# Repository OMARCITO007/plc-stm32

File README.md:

# plc-stm32
PLC básico basado en stm32 como controlador principal, con RS485, WIFI ESP32 y ETHERNET W5500

## Microncontrolador
* ⚛️ STM32F407VGT6.
* 🍏 ESP32-WROOM-32U.

## Voltaje de funcionamiento
* 🔌 24V.
* 🔌 Salida 5V.
## Caracteristicas
* 💙 x2 RS232.
* 💙 x1 RS485.
* 💙 x1 WIFI ESP32.
* 💙 x1 ETHERNET W5500.
* 💙 x1 EEPROM.
* 💙 x1 RTC.
* 💙 x1 USB para actualizar en modo BOOT y datos serial.
* ✔️ x12 entradas.
* ✔️ x16 salidas relé 2A.

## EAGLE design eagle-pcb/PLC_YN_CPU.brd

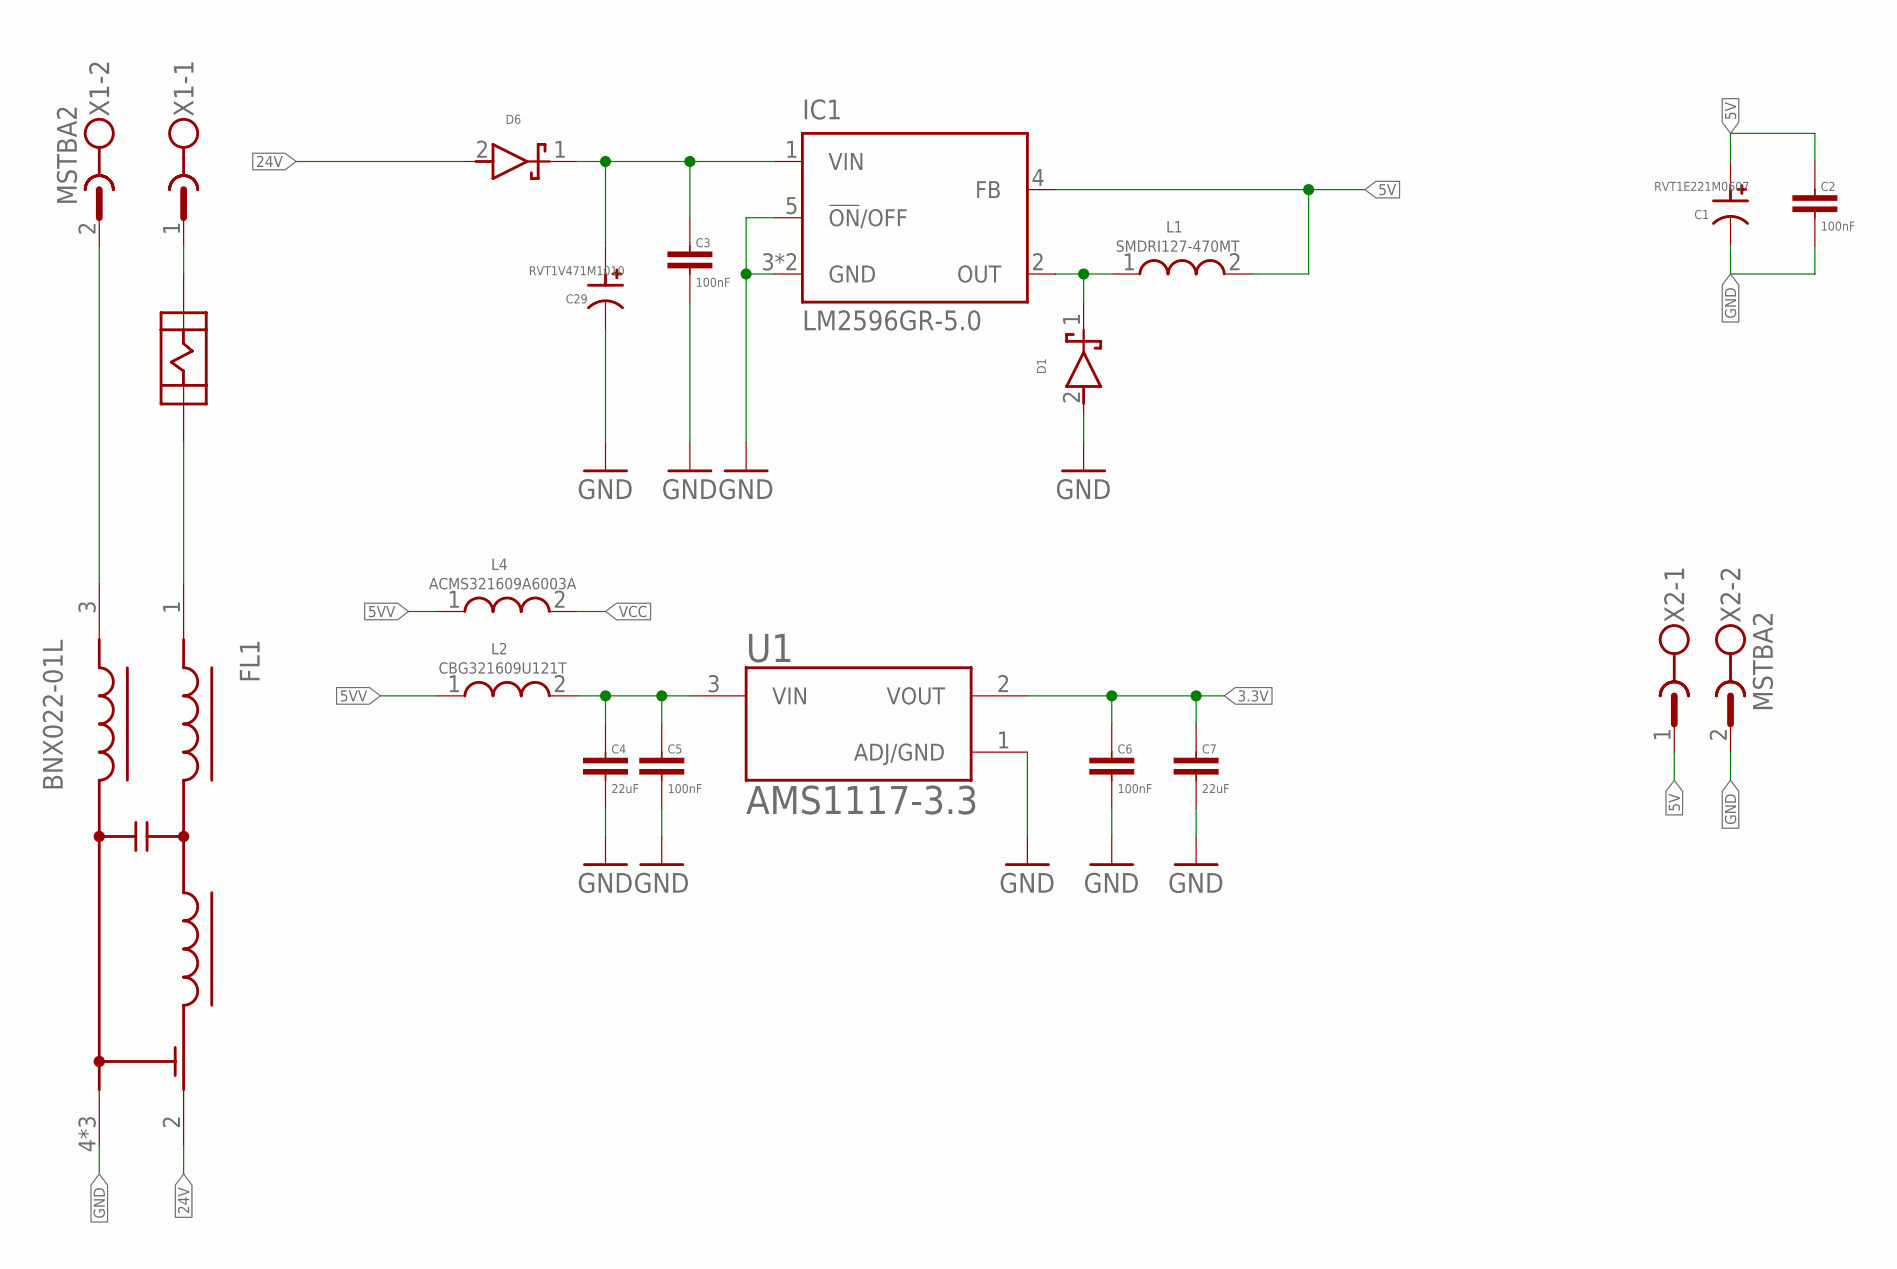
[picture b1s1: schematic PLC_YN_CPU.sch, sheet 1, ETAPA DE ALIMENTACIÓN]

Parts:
C1: RVT1E221M0607; CAP_100UF_6.3X7.7SMD
C2, C3, C5, C6: 100nF; C0603
C4, C7: 22uF; SMD_1206
C29: RVT1V471M1010; CAP_470UF_SMD_10X10.2
D1: SS36F; B360
D6: SS56; B360
F2: 3A; PORTAFUSIBLE
FL1: BNX022-01L; FIL_BNX022-01L
IC1: LM2596GR-5.0; TO263-5
L1: SMDRI127-470MT; IND
L2: CBG321609U121T; SMD_1206
L4: ACMS321609A6003A; SMD_1206
U1: AMS1117-3.3; SOT229P700X180-4N
X1, X2: MSTBA2

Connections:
3.3V: C6.1, C7.1, U1.2 (VOUT); also elsewhere on the board
5V: C1.P (1), C2.1, IC1.4 (FB), L1.2, X2.1; also elsewhere on the board
5VV: L2.1, L4.1; also elsewhere on the board
24V: D6.2, FL1.2 (CB); also elsewhere on the board
GND: C1.N (2), C2.2, C3.2, C4.2, C5.2, C6.2, C7.2, C29.N (2), D1.2, FL1.4 (CG), FL1.5 (CG), FL1.6 (CG), IC1.3 (GND), IC1.5 (!ON!/OFF), IC1.6 (GND), U1.1 (ADJ/GND), X2.2; also elsewhere on the board
unnamed: C4.1, C5.1, L2.2, U1.3 (VIN)
unnamed: C3.1, C29.P (1), D6.1, IC1.1 (VIN)
unnamed: D1.1, IC1.2 (OUT), L1.1
unnamed: F2.P$2, F2.P$4, X1.1
unnamed: FL1.3 (PSG), X1.2
unnamed: F2.P$1, F2.P$3, FL1.1 (B)
VCC: L4.2; also elsewhere on the board

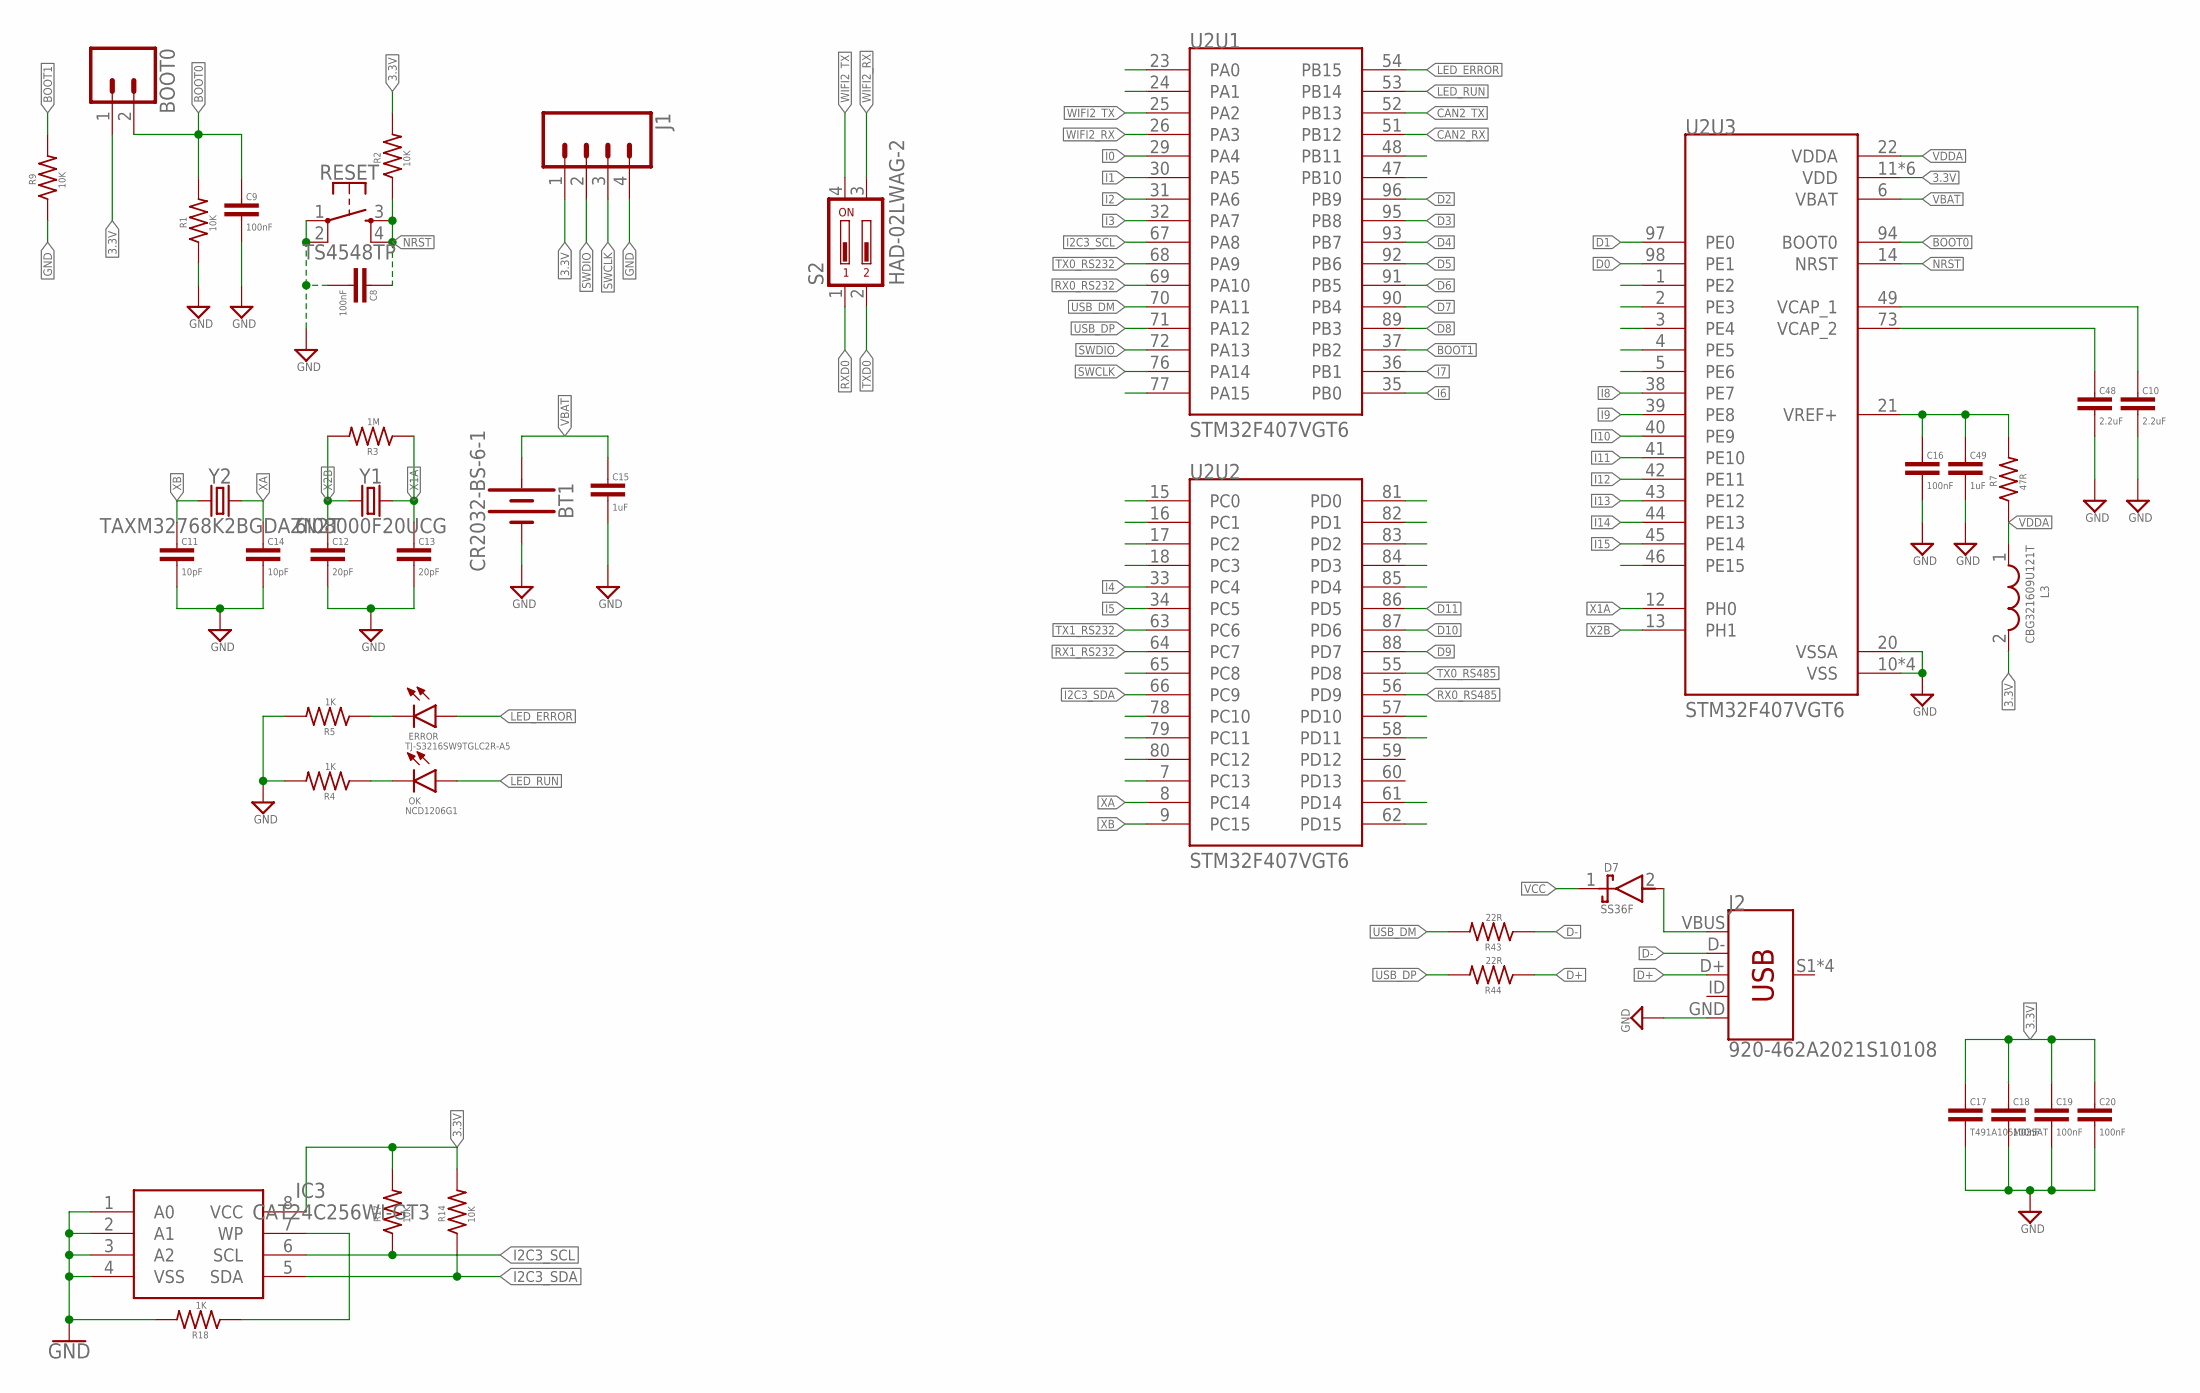
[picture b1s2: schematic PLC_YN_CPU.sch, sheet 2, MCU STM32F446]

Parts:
BOOT0: CONN_02; 1X02
BT1: CR2032-BS-6-1; BAT_CR2032_SMD
C8, C9, C16, C18, C19, C20: 100nF; C0603
C10, C48: 2.2uF; C0603
C11, C14: 10pF; C0603
C12, C13: 20pF; C0603
C15: 1uF; SMD_1206
C17: T491A105M035AT; SMD_1206
C49: 1uF; C0603
D7: SS36F; B360
ERROR: TJ-S3216SW9TGLC2R-A5; L1206
IC3: CAT24C256WI-GT3; SO08
J1: CONN_04; 1X04
J2: 920-462A2021S10108; USB-MINIB
L3: CBG321609U121T; SMD_1206
OK: NCD1206G1; L1206
R1, R2, R9, R14, R17: 10K; R0603
R3: 1M; R0603
R4, R5, R18: 1K; R0603
R7: 47R; R0603
R43, R44: 22R; R0603
RESET: TS4548TP; SWITCH
S2: HAD-02LWAG-2; CTS-219-02
U2: STM32F407VGT6; QFP50P1600X1600X160-100N
Y1: 6I08000F20UCG; CRYSTAL-SMD-5X3.2-2PAD
Y2: TAXM32768K2BGDAZN2T; CRYSTAL-SMD-2X6-CYL

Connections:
3.3V: BOOT0.1, C17.1, C18.1, C19.1, C20.1, IC3.8 (VCC), J1.1, L3.2, R2.2, R14.2, R17.2, U2.11 (VDD), U2.19 (VDD), U2.28 (VDD), U2.50 (VDD), U2.75 (VDD), U2.100 (VDD); also elsewhere on the board
BOOT0: BOOT0.2, C9.1, R1.2, U2.94 (BOOT0)
BOOT1: R9.2, U2.37 (PB2)
CAN2_RX: U2.51 (PB12)
CAN2_TX: U2.52 (PB13)
D0: U2.98 (PE1); also elsewhere on the board
D1: U2.97 (PE0); also elsewhere on the board
D2: U2.96 (PB9); also elsewhere on the board
D3: U2.95 (PB8); also elsewhere on the board
D4: U2.93 (PB7); also elsewhere on the board
D5: U2.92 (PB6); also elsewhere on the board
D6: U2.91 (PB5); also elsewhere on the board
D7: U2.90 (PB4); also elsewhere on the board
D8: U2.89 (PB3); also elsewhere on the board
D9: U2.88 (PD7); also elsewhere on the board
D10: U2.87 (PD6); also elsewhere on the board
D11: U2.86 (PD5); also elsewhere on the board
D+: J2.D+, R44.1
D-: J2.D-, R43.1
GND: BT1.N (-), C8.2, C9.2, C10.2, C11.2, C12.2, C13.2, C14.2, C15.2, C16.2, C17.2, C18.2, C19.2, C20.2, C48.2, C49.2, IC3.1 (A0), IC3.2 (A1), IC3.3 (A2), IC3.4 (VSS), J1.4, J2.GND, R1.1, R4.2, R5.2, R9.1, R18.2, RESET.1, RESET.2, U2.10 (VSS), U2.20 (VSSA), U2.27 (VSS), U2.74 (VSS), U2.99 (VSS); also elsewhere on the board
I0: U2.29 (PA4); also elsewhere on the board
I1: U2.30 (PA5); also elsewhere on the board
I2: U2.31 (PA6); also elsewhere on the board
I2C3_SCL: IC3.6 (SCL), R17.1, U2.67 (PA8)
I2C3_SDA: IC3.5 (SDA), R14.1, U2.66 (PC9)
I3: U2.32 (PA7); also elsewhere on the board
I4: U2.33 (PC4); also elsewhere on the board
I5: U2.34 (PC5); also elsewhere on the board
I6: U2.35 (PB0); also elsewhere on the board
I7: U2.36 (PB1); also elsewhere on the board
I8: U2.38 (PE7); also elsewhere on the board
I9: U2.39 (PE8); also elsewhere on the board
I10: U2.40 (PE9); also elsewhere on the board
I11: U2.41 (PE10); also elsewhere on the board
I12: U2.42 (PE11); also elsewhere on the board
I13: U2.43 (PE12); also elsewhere on the board
I14: U2.44 (PE13); also elsewhere on the board
I15: U2.45 (PE14); also elsewhere on the board
LED_ERROR: ERROR.A, U2.54 (PB15)
LED_RUN: OK.A, U2.53 (PB14)
unnamed: C10.1, U2.49 (VCAP_1)
unnamed: C48.1, U2.73 (VCAP_2)
unnamed: C16.1, C49.1, R7.2, U2.21 (VREF+)
unnamed: D7.2, J2.VBUS
unnamed: IC3.7 (WP), R18.1
unnamed: ERROR.C, R5.1
unnamed: OK.C, R4.1
NRST: C8.1, R2.1, RESET.3, RESET.4, U2.14 (NRST)
RX0_RS232: U2.69 (PA10); also elsewhere on the board
RX0_RS485: U2.56 (PD9); also elsewhere on the board
RX1_RS232: U2.64 (PC7); also elsewhere on the board
RXD0: S2.1; also elsewhere on the board
SWCLK: J1.3, U2.76 (PA14)
SWDIO: J1.2, U2.72 (PA13)
TX0_RS232: U2.68 (PA9); also elsewhere on the board
TX0_RS485: U2.55 (PD8); also elsewhere on the board
TX1_RS232: U2.63 (PC6); also elsewhere on the board
TXD0: S2.2; also elsewhere on the board
USB_DM: R43.2, U2.70 (PA11)
USB_DP: R44.2, U2.71 (PA12)
VBAT: BT1.P (+), C15.1, U2.6 (VBAT)
VCC: D7.1; also elsewhere on the board
VDDA: L3.1, R7.1, U2.22 (VDDA)
WIFI2_RX: S2.3, U2.26 (PA3)
WIFI2_TX: S2.4, U2.25 (PA2)
X1A: C13.1, R3.1, U2.12 (PH0), Y1.P$2 (2)
X2B: C12.1, R3.2, U2.13 (PH1), Y1.P$1 (1)
XA: C14.1, U2.8 (PC14), Y2.X2 (2)
XB: C11.1, U2.9 (PC15), Y2.X1 (1)

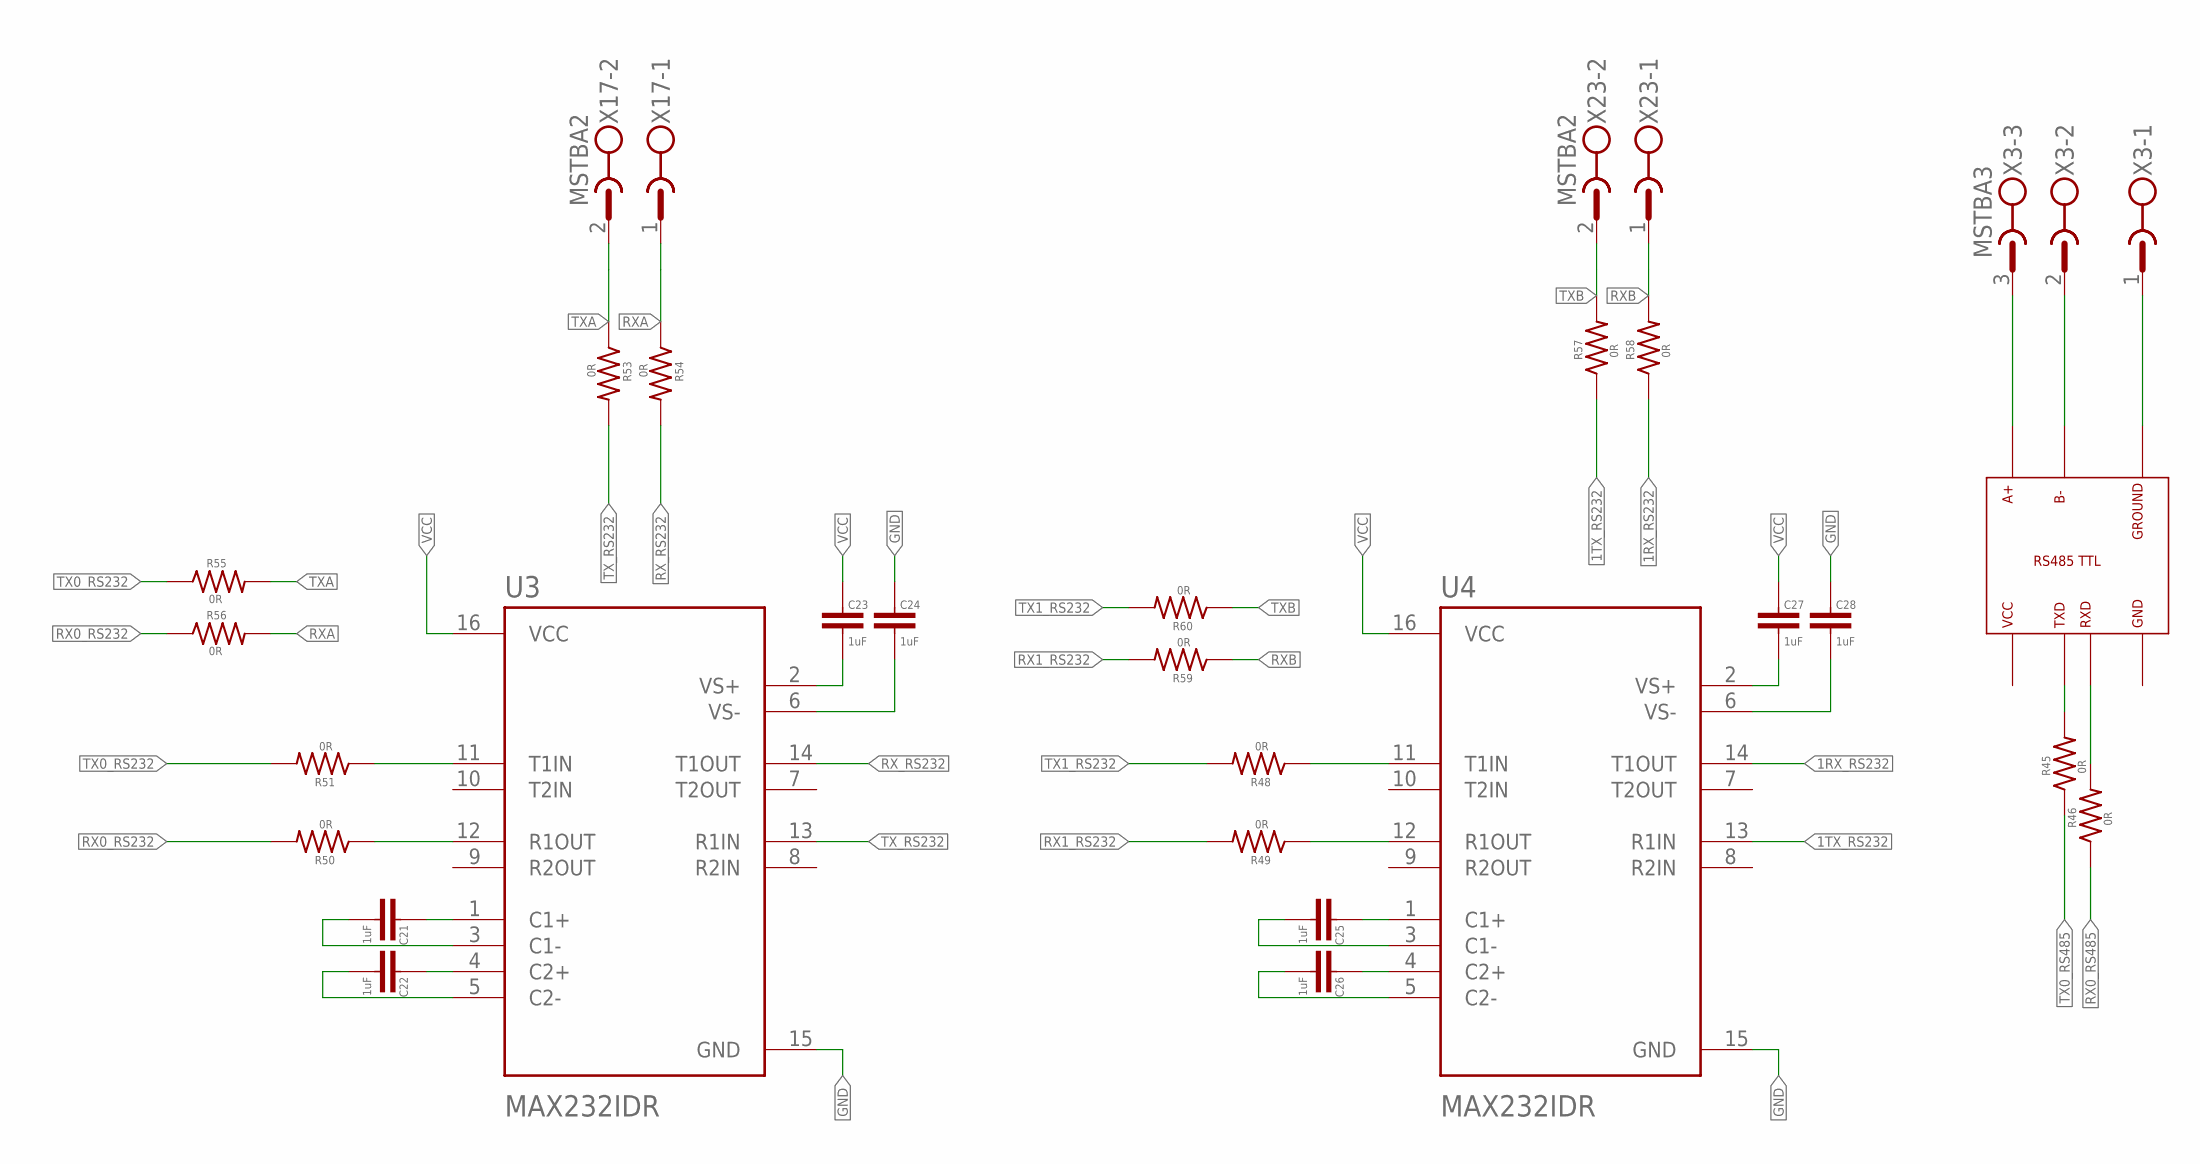
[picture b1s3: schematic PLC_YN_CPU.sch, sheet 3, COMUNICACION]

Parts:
C21, C22, C23, C24, C25, C26, C27, C28: 1uF; C0603
R45, R46, R48, R49, R50, R51, R53, R54, R55, R56, R57, R58, R59, R60: 0R; R0603
U3, U4: MAX232IDR; SOIC127P600X175-16N
U5: RS485; RS485TTL
X3: MSTBA3
X17, X23: MSTBA2

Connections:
1RX_RS232: R58.1, U4.14 (T1OUT)
1TX_RS232: R57.1, U4.13 (R1IN)
GND: C24.1, C28.1, U3.15 (GND), U4.15 (GND), U5.GND; also elsewhere on the board
unnamed: U5.A+, X3.3
unnamed: R45.2, U5.TXD
unnamed: U5.B-, X3.2
unnamed: U5.GROUND, X3.1
unnamed: C21.1, U3.1 (C1+)
unnamed: C21.2, U3.3 (C1-)
unnamed: C22.1, U3.4 (C2+)
unnamed: C22.2, U3.5 (C2-)
unnamed: C25.1, U4.1 (C1+)
unnamed: C23.2, U3.2 (VS+)
unnamed: C24.2, U3.6 (VS-)
unnamed: C25.2, U4.3 (C1-)
unnamed: C26.1, U4.4 (C2+)
unnamed: C26.2, U4.5 (C2-)
unnamed: C27.2, U4.2 (VS+)
unnamed: C28.2, U4.6 (VS-)
unnamed: R46.2, U5.RXD
unnamed: R48.1, U4.11 (T1IN)
unnamed: R49.1, U4.12 (R1OUT)
unnamed: R50.1, U3.12 (R1OUT)
unnamed: R51.1, U3.11 (T1IN)
RX0_RS232: R50.2, R56.1; also elsewhere on the board
RX0_RS485: R46.1; also elsewhere on the board
RX1_RS232: R49.2, R59.2; also elsewhere on the board
RXA: R54.1, R56.2, X17.1
RXB: R58.2, R59.1, X23.1
RX_RS232: R54.2, U3.14 (T1OUT)
TX0_RS232: R51.2, R55.1; also elsewhere on the board
TX0_RS485: R45.1; also elsewhere on the board
TX1_RS232: R48.2, R60.2; also elsewhere on the board
TXA: R53.1, R55.2, X17.2
TXB: R57.2, R60.1, X23.2
TX_RS232: R53.2, U3.13 (R1IN)
VCC: C23.1, C27.1, U3.16 (VCC), U4.16 (VCC), U5.VCC; also elsewhere on the board

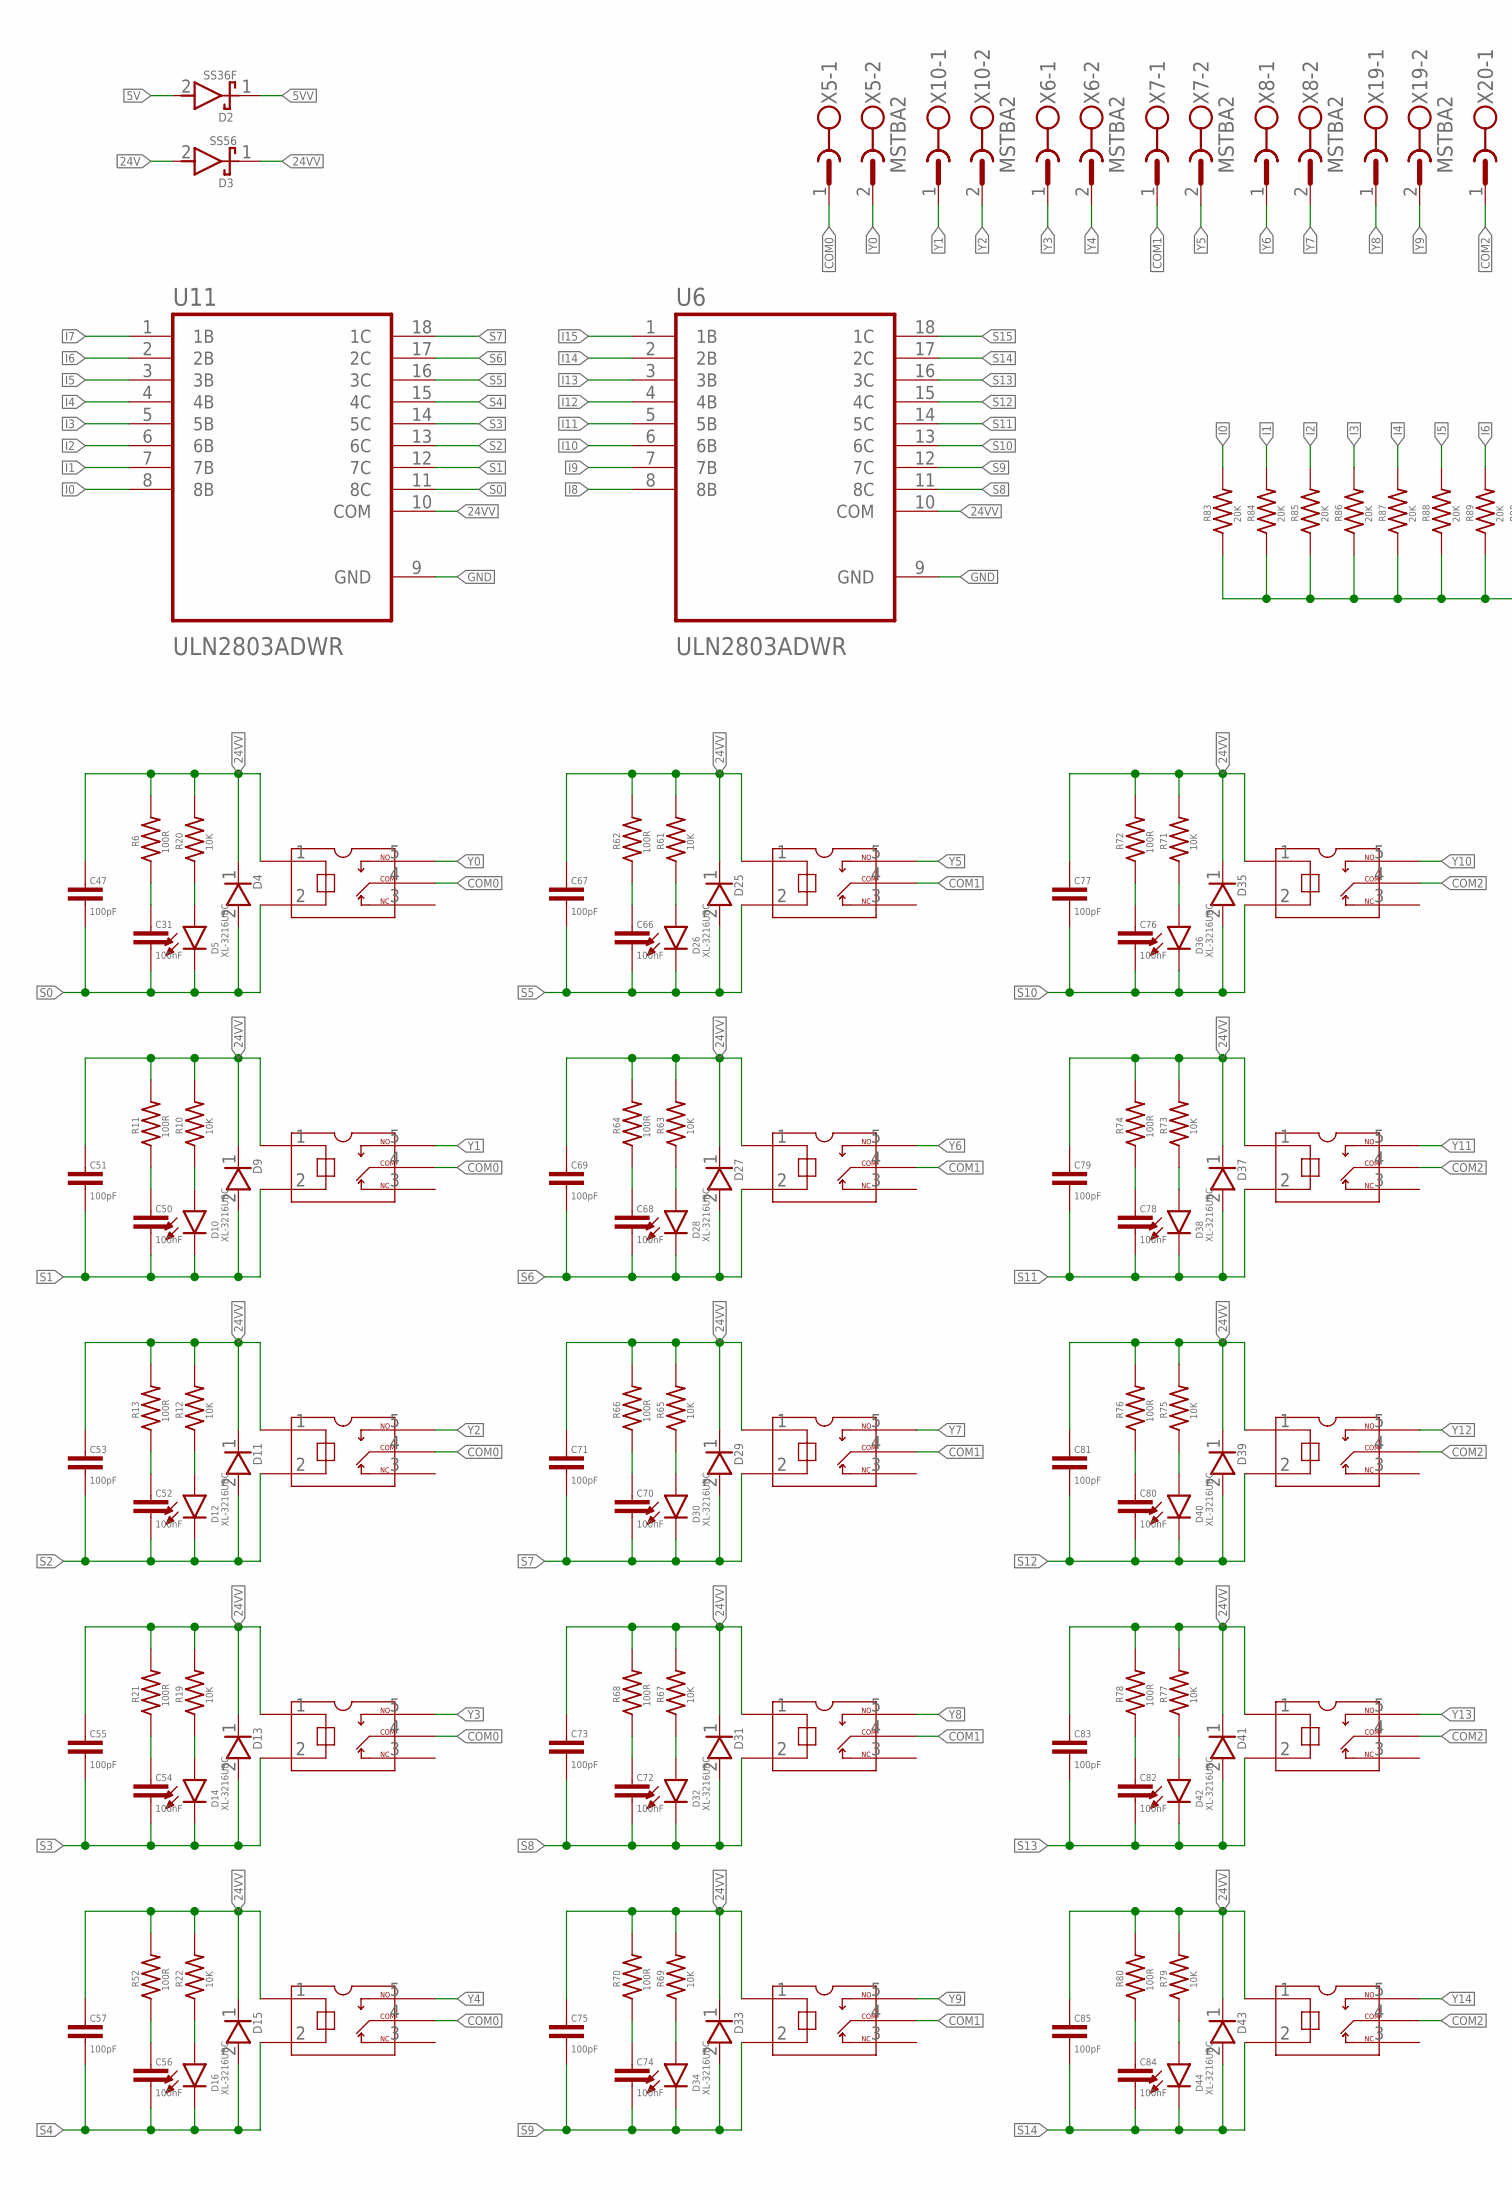
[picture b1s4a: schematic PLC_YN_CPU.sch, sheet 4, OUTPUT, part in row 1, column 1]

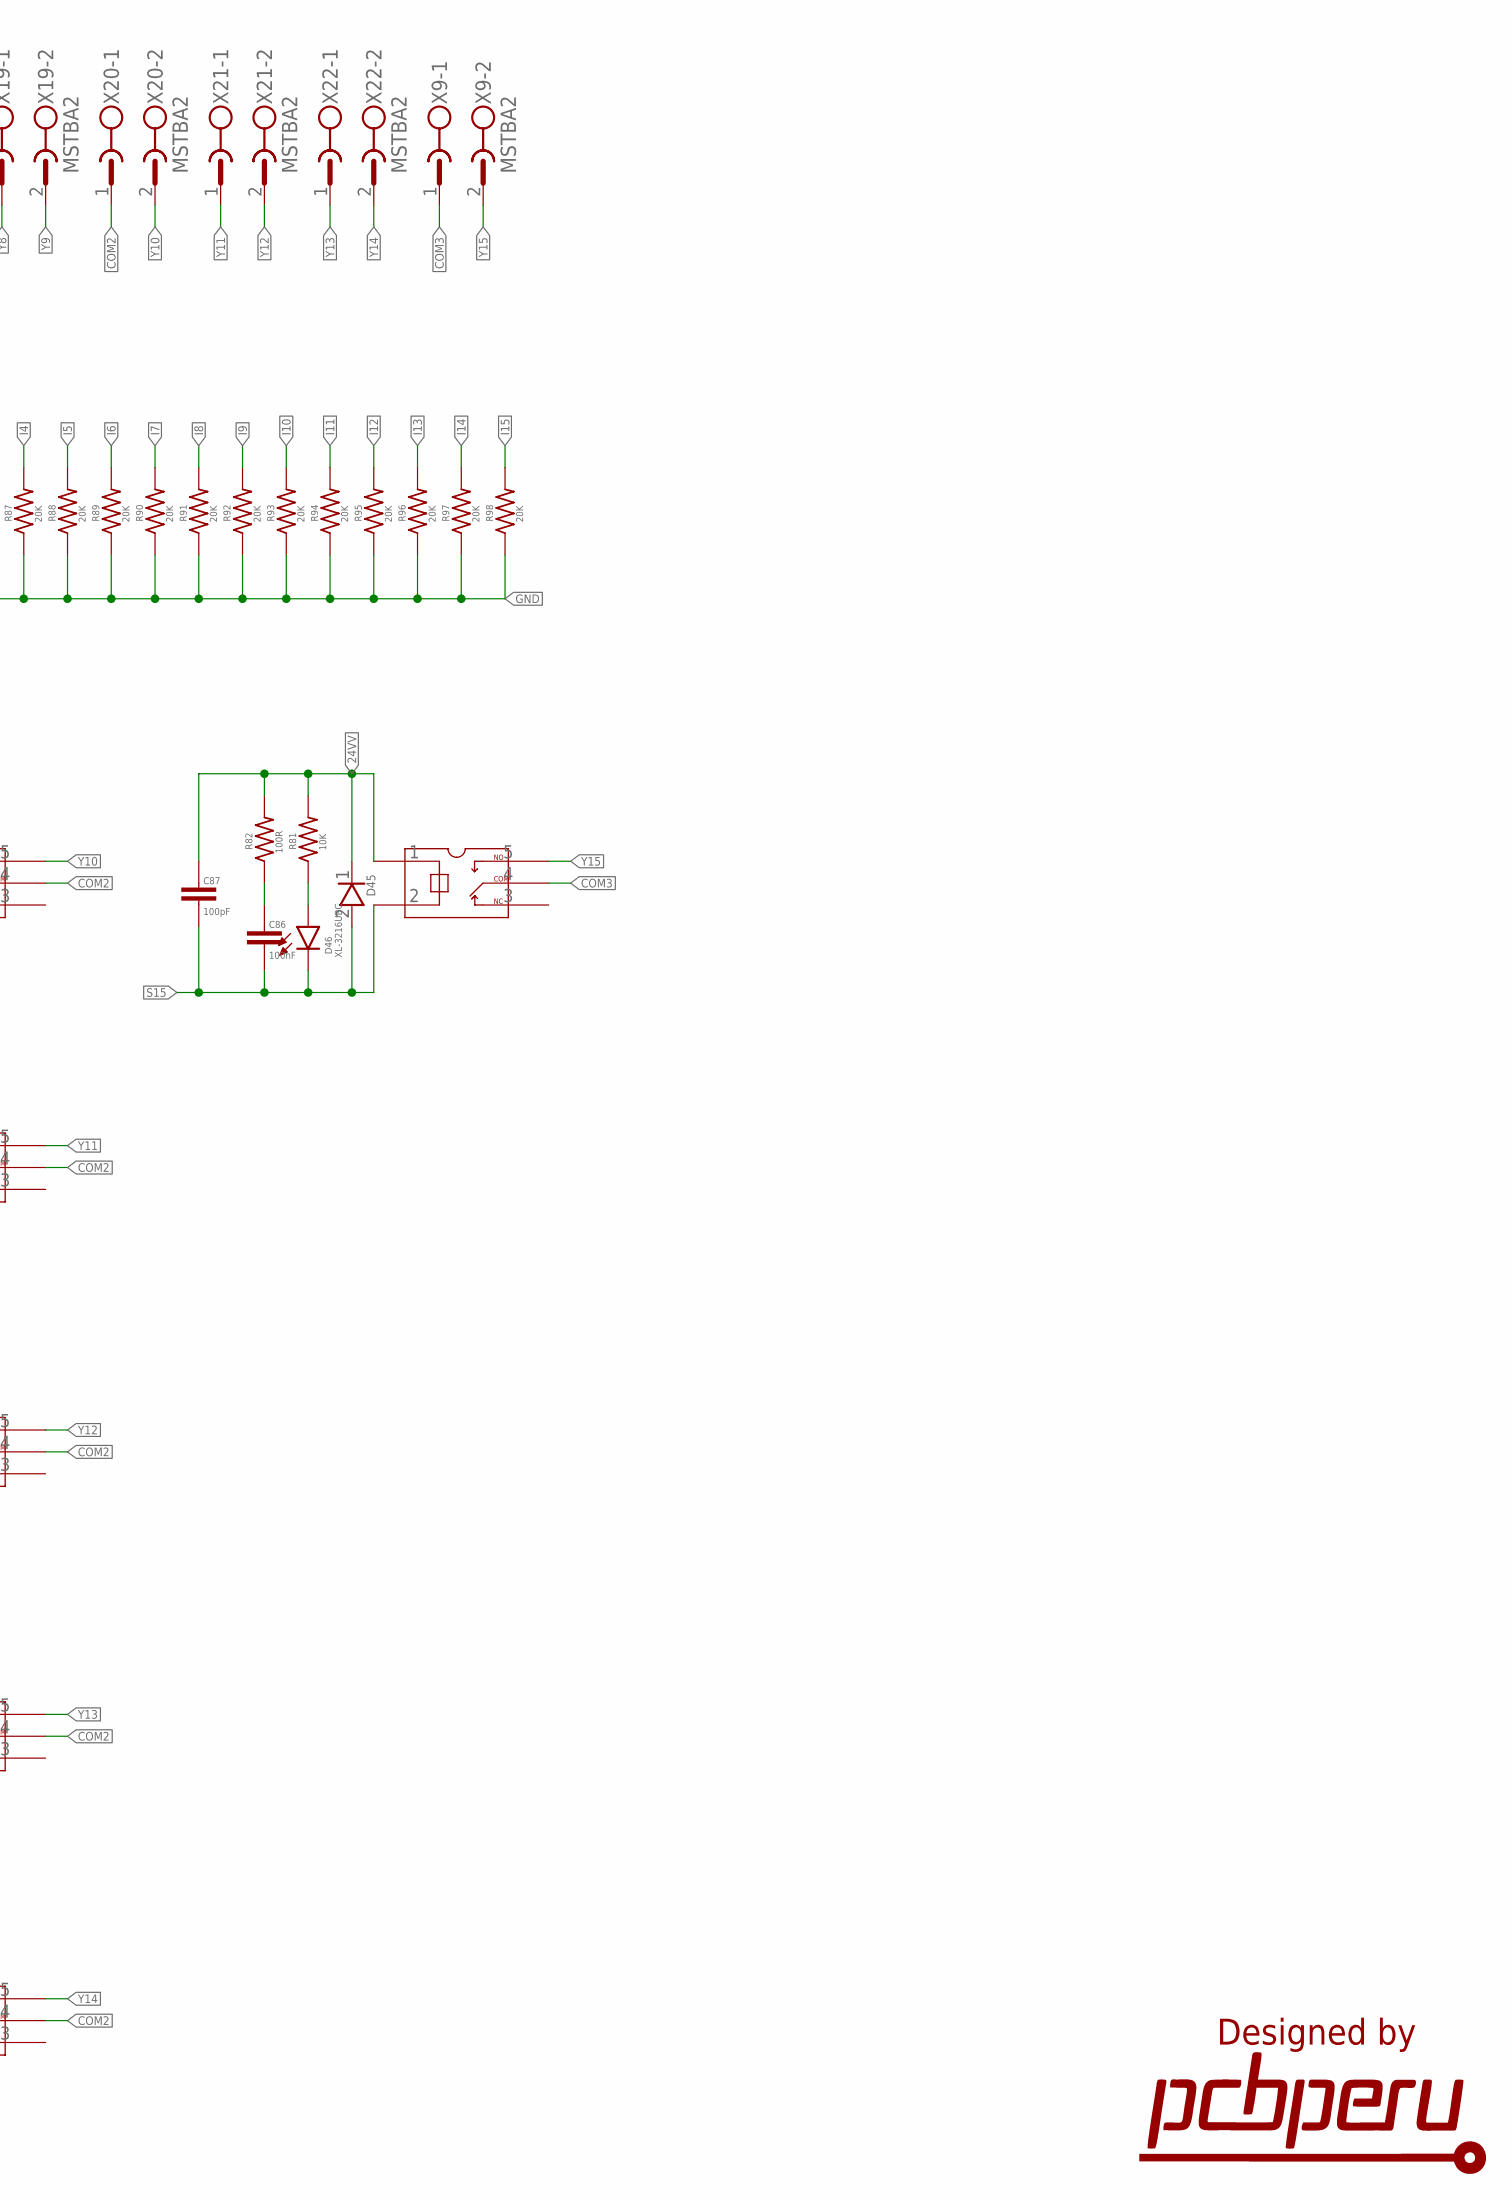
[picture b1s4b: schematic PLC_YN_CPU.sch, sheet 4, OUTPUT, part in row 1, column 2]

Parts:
C31, C50, C52, C54, C56, C66, C68, C70, C72, C74, C76, C78, C80, C82, C84, C86: 100nF; C0603
C47, C51, C53, C55, C57, C67, C69, C71, C73, C75, C77, C79, C81, C83, C85, C87: 100pF; C0603
D2: SS36F; B360
D3: SS56; B360
D4, D9, D11, D13, D15, D25, D27, D29, D31, D33, D35, D37, D39, D41, D43, D45: 1N4148W-13-F; SOD3716X145N
D5, D10, D12, D14, D16, D26, D28, D30, D32, D34, D36, D38, D40, D42, D44, D46: XL-3216UBC; L1206
R6, R11, R13, R21, R52, R62, R64, R66, R68, R70, R72, R74, R76, R78, R80, R82: 100R; R0603
R10, R12, R19, R20, R22, R61, R63, R65, R67, R69, R71, R73, R75, R77, R79, R81: 10K; R0603
R83, R84, R85, R86, R87, R88, R89, R90, R91, R92, R93, R94, R95, R96, R97, R98: 20K; R0603
RL1, RL3, RL4, RL5, RL6, RL11, RL12, RL13, RL14, RL15, RL16, RL17, RL18, RL19, RL20, RL21: HF41F
U6, U11: ULN2803ADWR; SOIC127P1030X265-18N
X5, X6, X7, X8, X9, X10, X19, X20, X21, X22: MSTBA2

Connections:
5V: D2.2; also elsewhere on the board
5VV: D2.1; also elsewhere on the board
24V: D3.2; also elsewhere on the board
24VV: C47.1, C51.1, C53.1, C55.1, C57.1, C67.1, C69.1, C71.1, C73.1, C75.1, C77.1, C79.1, C81.1, C83.1, C85.1, C87.1, D3.1, D4.1 (K), D9.1 (K), D11.1 (K), D13.1 (K), D15.1 (K), D25.1 (K), D27.1 (K), D29.1 (K), D31.1 (K), D33.1 (K), D35.1 (K), D37.1 (K), D39.1 (K), D41.1 (K), D43.1 (K), D45.1 (K), R6.2, R10.2, R11.2, R12.2, R13.2, R19.2, R20.2, R21.2, R22.2, R52.2, R61.2, R62.2, R63.2, R64.2, R65.2, R66.2, R67.2, R68.2, R69.2, R70.2, R71.2, R72.2, R73.2, R74.2, R75.2, R76.2, R77.2, R78.2, R79.2, R80.2, R81.2, R82.2, RL1.1, RL3.1, RL4.1, RL5.1, RL6.1, RL11.1, RL12.1, RL13.1, RL14.1, RL15.1, RL16.1, RL17.1, RL18.1, RL19.1, RL20.1, RL21.1, U6.10 (COM), U11.10 (COM)
COM0: RL1.4, RL3.4, RL4.4, RL5.4, RL6.4, X5.1
COM1: RL11.4, RL12.4, RL13.4, RL14.4, RL15.4, X7.1
COM2: RL16.4, RL17.4, RL18.4, RL19.4, RL20.4, X20.1
COM3: RL21.4, X9.1
GND: R83.1, R84.1, R85.1, R86.1, R87.1, R88.1, R89.1, R90.1, R91.1, R92.1, R93.1, R94.1, R95.1, R96.1, R97.1, R98.1, U6.9 (GND), U11.9 (GND); also elsewhere on the board
I0: R83.2, U11.8 (8B); also elsewhere on the board
I1: R84.2, U11.7 (7B); also elsewhere on the board
I2: R85.2, U11.6 (6B); also elsewhere on the board
I3: R86.2, U11.5 (5B); also elsewhere on the board
I4: R87.2, U11.4 (4B); also elsewhere on the board
I5: R88.2, U11.3 (3B); also elsewhere on the board
I6: R89.2, U11.2 (2B); also elsewhere on the board
I7: R90.2, U11.1 (1B); also elsewhere on the board
I8: R91.2, U6.8 (8B); also elsewhere on the board
I9: R92.2, U6.7 (7B); also elsewhere on the board
I10: R93.2, U6.6 (6B); also elsewhere on the board
I11: R94.2, U6.5 (5B); also elsewhere on the board
I12: R95.2, U6.4 (4B); also elsewhere on the board
I13: R96.2, U6.3 (3B); also elsewhere on the board
I14: R97.2, U6.2 (2B); also elsewhere on the board
I15: R98.2, U6.1 (1B); also elsewhere on the board
unnamed: C31.1, R6.1
unnamed: D10.A, R10.1
unnamed: D5.A, R20.1
unnamed: C50.1, R11.1
unnamed: D12.A, R12.1
unnamed: C52.1, R13.1
unnamed: D14.A, R19.1
unnamed: C54.1, R21.1
unnamed: D16.A, R22.1
unnamed: C56.1, R52.1
unnamed: D26.A, R61.1
unnamed: C66.1, R62.1
unnamed: D28.A, R63.1
unnamed: C68.1, R64.1
unnamed: D30.A, R65.1
unnamed: C70.1, R66.1
unnamed: D32.A, R67.1
unnamed: C72.1, R68.1
unnamed: D34.A, R69.1
unnamed: C74.1, R70.1
unnamed: D36.A, R71.1
unnamed: C76.1, R72.1
unnamed: D38.A, R73.1
unnamed: C78.1, R74.1
unnamed: D40.A, R75.1
unnamed: C80.1, R76.1
unnamed: D42.A, R77.1
unnamed: C82.1, R78.1
unnamed: D44.A, R79.1
unnamed: C84.1, R80.1
unnamed: D46.A, R81.1
unnamed: C86.1, R82.1
S0: C31.2, C47.2, D4.2 (A), D5.C, RL1.2, U11.11 (8C)
S1: C50.2, C51.2, D9.2 (A), D10.C, RL3.2, U11.12 (7C)
S2: C52.2, C53.2, D11.2 (A), D12.C, RL4.2, U11.13 (6C)
S3: C54.2, C55.2, D13.2 (A), D14.C, RL5.2, U11.14 (5C)
S4: C56.2, C57.2, D15.2 (A), D16.C, RL6.2, U11.15 (4C)
S5: C66.2, C67.2, D25.2 (A), D26.C, RL11.2, U11.16 (3C)
S6: C68.2, C69.2, D27.2 (A), D28.C, RL12.2, U11.17 (2C)
S7: C70.2, C71.2, D29.2 (A), D30.C, RL13.2, U11.18 (1C)
S8: C72.2, C73.2, D31.2 (A), D32.C, RL14.2, U6.11 (8C)
S9: C74.2, C75.2, D33.2 (A), D34.C, RL15.2, U6.12 (7C)
S10: C76.2, C77.2, D35.2 (A), D36.C, RL16.2, U6.13 (6C)
S11: C78.2, C79.2, D37.2 (A), D38.C, RL17.2, U6.14 (5C)
S12: C80.2, C81.2, D39.2 (A), D40.C, RL18.2, U6.15 (4C)
S13: C82.2, C83.2, D41.2 (A), D42.C, RL19.2, U6.16 (3C)
S14: C84.2, C85.2, D43.2 (A), D44.C, RL20.2, U6.17 (2C)
S15: C86.2, C87.2, D45.2 (A), D46.C, RL21.2, U6.18 (1C)
Y0: RL1.5, X5.2
Y1: RL3.5, X10.1
Y2: RL4.5, X10.2
Y3: RL5.5, X6.1
Y4: RL6.5, X6.2
Y5: RL11.5, X7.2
Y6: RL12.5, X8.1
Y7: RL13.5, X8.2
Y8: RL14.5, X19.1
Y9: RL15.5, X19.2
Y10: RL16.5, X20.2
Y11: RL17.5, X21.1
Y12: RL18.5, X21.2
Y13: RL19.5, X22.1
Y14: RL20.5, X22.2
Y15: RL21.5, X9.2

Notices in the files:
parts and their libraries:
SparkFun-Connectors: Licensing: Creative Commons ShareAlike 4.0 International - https://creativecommons.org/licenses/by-sa/4.0
SparkFun: Licensing: CC v3.0 Share-Alike You are welcome to use this library for commercial purposes.
